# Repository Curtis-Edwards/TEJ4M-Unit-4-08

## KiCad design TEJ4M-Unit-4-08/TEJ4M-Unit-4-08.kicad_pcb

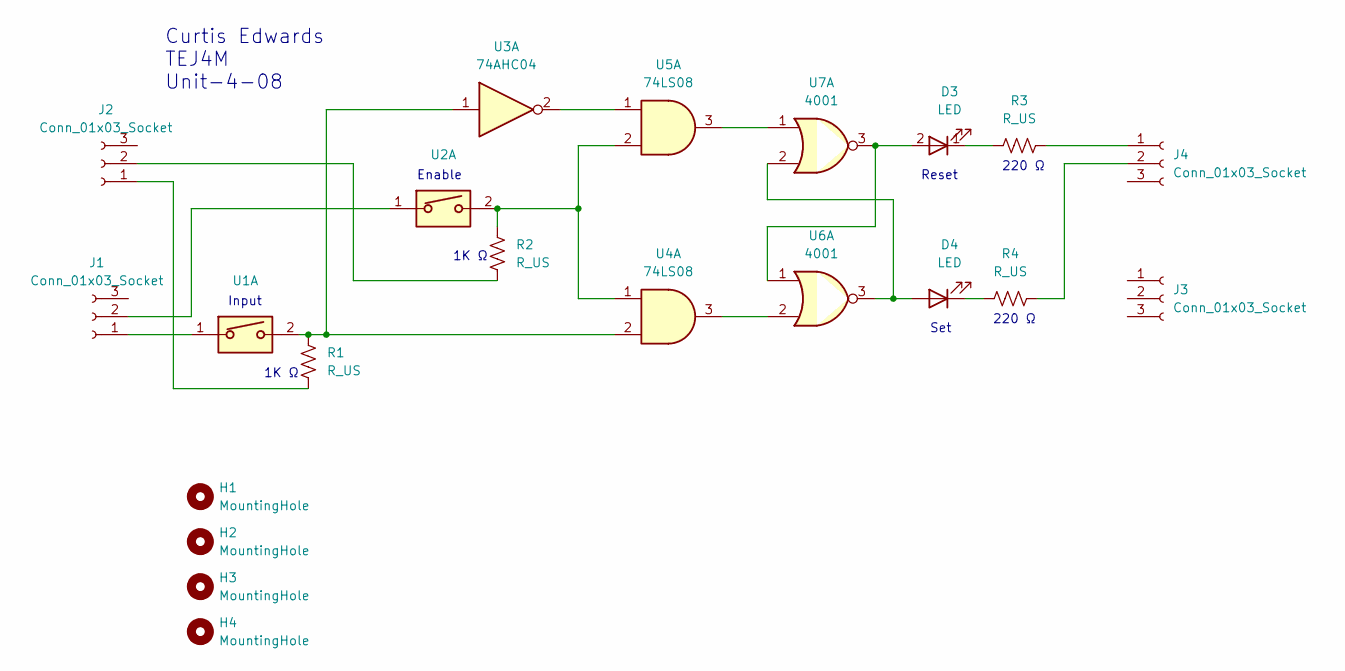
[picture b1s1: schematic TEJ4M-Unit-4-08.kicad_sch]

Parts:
D3, D4: LED; LED_D3.0mm_Horizontal_O1.27mm_Z2.0mm
H1, H2, H3, H4: MountingHole; MountingHole_2.5mm
J1, J2, J3, J4: Conn_01x03_Socket; PinSocket_1x03_P1.27mm_Vertical
R1, R2, R3, R4: R_US; R_Axial_DIN0207_L6.3mm_D2.5mm_P7.62mm_Horizontal
U1, U2: ADG417BN; SW_PUSH_6mm
U3: 74AHC04; DIP-8_W7.62mm
U4, U5: 74LS08; DIP-8_W7.62mm
U6, U7: 4001; DIP-8_W7.62mm

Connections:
unnamed: D3.2 (A), U6.1, U7.3
unnamed: D3.1 (K), R3.1
unnamed: D4.2 (A), U6.3, U7.2
unnamed: D4.1 (K), R4.1
unnamed: J1.1, U1.1
unnamed: J1.2, U2.1
unnamed: J2.1, R1.2
unnamed: J2.2, R2.2
unnamed: J4.1, R3.2
unnamed: J4.2, R4.2
unnamed: R1.1, U1.2, U3.1, U4.2
unnamed: R2.1, U2.2, U4.1, U5.2
unnamed: U3.2, U5.1
unnamed: U4.3, U6.2
unnamed: U5.3, U7.1

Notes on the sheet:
Reset
Input
220 Ω
1K Ω
Enable
Curtis Edwards TEJ4M Unit-4-08
Set

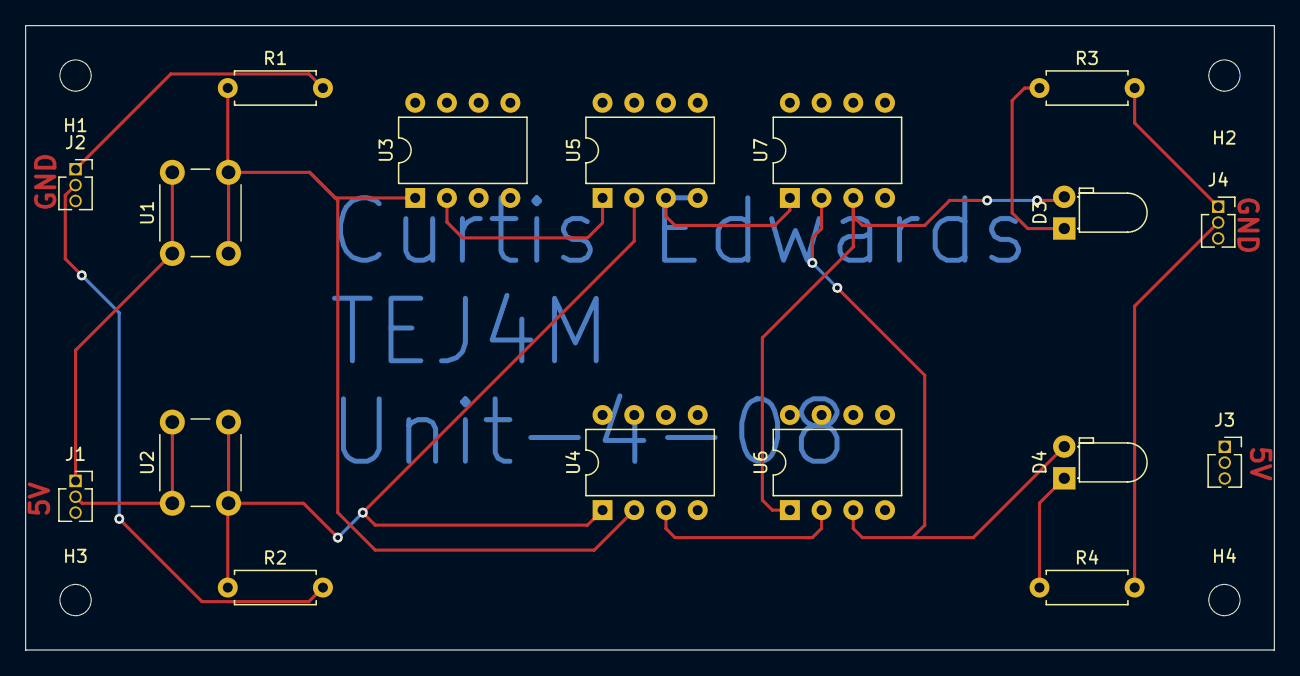
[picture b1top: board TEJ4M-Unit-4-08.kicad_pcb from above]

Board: 2 copper layers, 100.0 x 50.0 mm, 21 parts (0 on the bottom side), 15 nets.
